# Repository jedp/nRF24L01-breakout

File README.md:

# nRF24L01+ breakout board

The Nordic Semiconductor nRF24L01.

Antenna constructed according to AN043.

## BOM

- C1: 22pF 0402
- C2: 22pF 0402
- C3: 2.2nF 0402
- C7: 33nF 0402
- C8: 1nF 0402
- C9: 10nF 0402
- C10: 4.7µF 0603
- J1: Conn 01x04 Female 2.54mm
- J2: Conn 01x04 Female 2.54mm
- R1: 1M 0402
- R2: 22k 0402
- R3: 0k 0603
- U1: NRF24L01 QFN-20
- U2: Antenna PCB 2.4GHz 50Ohm
- U3: Balun 2450BM14A0002 Johanson 1.6x0.8mm
- Y1: Crystal GND24 Small SMD_2520-4Pin 2.5x2.0mm

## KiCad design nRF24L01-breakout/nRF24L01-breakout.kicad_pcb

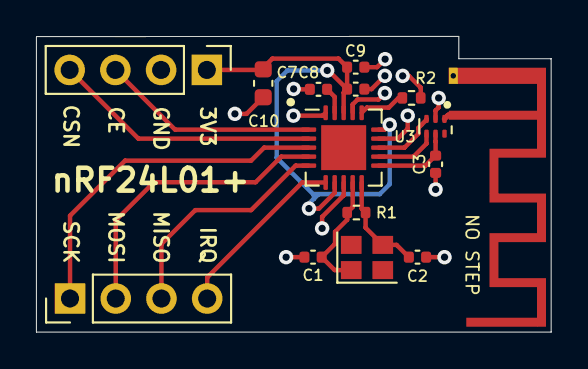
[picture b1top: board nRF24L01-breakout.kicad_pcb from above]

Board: 2 copper layers, 28.6 x 16.4 mm, 16 parts (1 on the bottom side), 17 nets.

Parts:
C1, C2: 22pF; C_0402_1005Metric
C3: 2.2nF; C_0402_1005Metric
C7: 33nF; C_0402_1005Metric
C8: 1nF; C_0402_1005Metric
C9: 10nF; C_0402_1005Metric
C10: 4.7µF; C_0603_1608Metric
J1, J2: Conn_01x04_Female; PinHeader_1x04_P2.54mm_Vertical
R1: 1M; R_0402_1005Metric
R2: 22k; R_0402_1005Metric
R3: 0k; R_0603_1608Metric
U1: NRF24L01; QFN-20-1EP_4x4mm_P0.5mm_EP2.5x2.5mm
U2: Antenna_PCB_2.4GHz_50Ohm
U3: Balun_2450BM14A0002; Balun_Johanson_1.6x0.8mm
Y1: Crystal_GND24_Small; Crystal_SMD_2520-4Pin_2.5x2.0mm

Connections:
ANT1: U1.12 (ANT1), U3.4 (Bal2)
ANT2: U1.13 (ANT2), U3.3 (Bal1)
CE: J1.3, U1.1 (CE)
CSN: J1.4, U1.2 (CSN)
GND: C1.2, C2.2, C3.2, C7.2, C8.2, C9.2, C10.2, J1.2, R2.2, R3.2, U1.8 (VSS), U1.14 (VSS), U1.17 (VSS), U1.20 (VSS), U3.2 (GND)
IRQ: J2.4, U1.6 (IRQ)
MISO: J2.3, U1.5 (MISO)
MOSI: J2.2, U1.4 (MOSI)
unnamed: C7.1, U1.19 (DVDD)
unnamed: R2.1, U1.16 (IREF)
unnamed: R3.1, U2.2 (GND)
unnamed: U2.1 (ANT), U3.1 (Unbal)
SCK: J2.1, U1.3 (SCK)
VDD: C8.1, C9.1, C10.1, J1.1, U1.7 (VDD), U1.15 (VDD), U1.18 (VDD)
VDD_PA: C3.1, U1.11 (VDD_PA), U3.5 (DC)
XC1: C2.1, R1.1, U1.10 (XC1), Y1.3
XC2: C1.1, R1.2, U1.9 (XC2), Y1.1

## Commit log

2023-03-06 KiCad schematic and layout; Custom footprint for AN043 antenna.
2023-03-06 Ignore auto-save files
2023-03-06 Init
2023-03-10 Use Johanson 2450BM14A0002 matched balun
2023-04-08 Fix balun footprint; Make board smaller
2023-04-08 Update screenshot
2023-04-08 Move a via away from a trace
2023-04-08 Added bom to readme
2023-04-09 Spread out signal traces
